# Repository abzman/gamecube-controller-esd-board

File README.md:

# gamecube-controller-esd-board

deprecated, moved all boards to one repo here: https://github.com/abzman/wii-mini-boards

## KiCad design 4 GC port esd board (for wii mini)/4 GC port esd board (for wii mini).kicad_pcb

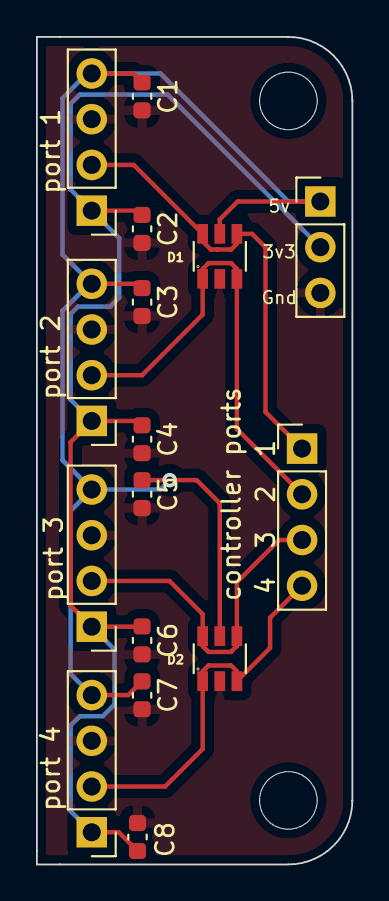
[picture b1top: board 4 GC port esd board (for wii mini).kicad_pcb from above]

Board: 2 copper layers, 17.5 x 46.0 mm, 16 parts (0 on the bottom side), 7 nets.

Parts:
C1, C2, C3, C4, C5, C6, C7, C8: C; C_0603_1608Metric
D1, D2: WE-TVS_824014; WE-TVS_SOT23-6L
J1: port 4; PinHeader_1x04_P2.54mm_Vertical
J2: port 1; PinHeader_1x04_P2.54mm_Vertical
J3: port 2; PinHeader_1x04_P2.54mm_Vertical
J4: port 3; PinHeader_1x04_P2.54mm_Vertical
J5: power; PinHeader_1x03_P2.54mm_Vertical
J6: controller ports; PinHeader_1x04_P2.54mm_Vertical

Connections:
+3V3: C2.1, C4.1, C6.1, C8.1, J1.1, J2.1, J3.1, J4.1, J5.2
+5V: C1.1, C3.1, C5.1, C7.1, D1.5, D2.5, J1.4, J2.4, J3.4, J4.4, J5.1
GND: C1.2, C2.2, C3.2, C4.2, C5.2, C6.2, C7.2, C8.2, D1.2, D2.2, J1.3, J2.3, J3.3, J4.3, J5.3
unnamed: D1.1, D1.3, J3.2, J6.2
unnamed: D1.4, D1.6, J2.2, J6.1
unnamed: D2.1, D2.3, J1.2, J6.4
unnamed: D2.4, D2.6, J4.2, J6.3

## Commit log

2022-02-19 first board, using the WE-TVS_824014
2022-02-19 updated silk
2022-02-22 silk fix
2022-03-13 generated gerbers
2022-03-14 gerber zip
2022-11-25 added gitignore
2023-11-03 moved to other repo
